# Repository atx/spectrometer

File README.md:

# Alpha Spectrometer

Alpha spectrometer developed during my internship at the [IEAP](http://www.utef.cvut.cz/ieap).

Pu-239 Am-241 Cm-244 spectrum (on bare die BPW34 in vacuum)

## Protocol

### General structure

```
|----------|---------
|   type   | content...
|----------|---------
```

If the device receives a packet with invalid type, it responds with an ERROR
packet with EUNKNOWN error type.

### Host->Device

#### NOP

This does not do anything, it is recommended to send a bunch of NOPs on opening
the serial port to flush any data which might have been left in the device input
buffer.
```
|----------|
|   0x01   |
|----------|
```
#### PING

Used by host to check whether the device is alive. Device should respond with PONG.
```
|----------|
|   0x02   |
|----------|
```
#### GET

Used by host to get basic properties. Device should respond with GETRESP.
```
|----------|---------|
|   0x03   | propid  |
|----------|---------|
```
#### SET

Used by host to set basic properties. Propval length depends on the property being
set. Note that multi byte values should be sent in little endian.
```
|----------|---------|----------
|   0x04   | propid  | propval...
|----------|---------|----------
```
#### START

Start sampling and sending events.
```
|----------|
|   0x05   |
|----------|
```
#### END

End sampling and sending events.
```
|----------|
|   0x06   |
|----------|
```
### Device->Host

The most significant bit of the type field is always set to 1.

#### PONG

Sent as response to host PING.
```
|----------|
|   0x82   |
|----------|
```
#### EVENT

Send event (little endian).
```
|----------|----------|----------|
|   0x87   |   low    |   high   |
|----------|----------|----------|
```
#### GETRESP
```
|----------|----------|----------
|   0x83   |  propid  |  value...
|----------|----------|----------
```
The value length depends on the propid and the byte order is little endian.

#### WAVE

Sends event waveform. This is currently not yet implemented.
```
|----------|----------|----------
|   0x88   |  length  |  <length> samples, 2 bytes each, Big endian
|----------|----------|----------
```
#### ERROR
```
|----------|----------|
|   0xff   |  errno   |
|----------|----------|
```
Sent on errors.
errno:
  =  1  EUNKNOWN
    -- Sent on unknown packet type received
  =  2  EINKEY
    -- Sent on invalid key in GET/SET packet
  =  3  EINOP
    -- Sent on invalid operation on an existing key (unsuported read/write)

### Properties

#### PROP_FW (0x01)
length = 2

Firmware version version.

#### PROP_THRESH (0x02)
length = 2

Event trigger threshold.

#### PROP_BIAS (0x03)
length = 1

Set to 1 if the internal bias generator should be enabled.

#### PROP_AMP (0x04)
length = 1

Set to 1 if the internal x6 amplifier should be enabled.

#### PROP_RTHRESH (0x05)
length = 2

If the value is > 0, the events are further filtered based on whether their falling edge
is at least N samples longer than the rising edge.

#### PROP_SERNO (0x06)
length = 2

Serial number of the device. Set at compile time using `make SERNO=X`

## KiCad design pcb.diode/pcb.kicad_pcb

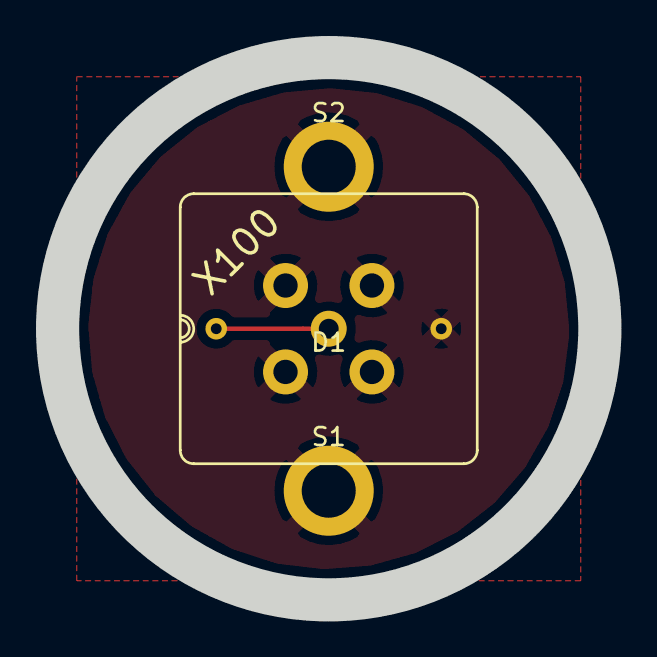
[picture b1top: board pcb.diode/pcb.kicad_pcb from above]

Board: 2 copper layers, 30.1 x 30.1 mm, 4 parts (1 on the bottom side), 2 nets.

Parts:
D1: X100; X100-7-THD
J1: SMA; SMA_STRAIGHT_PCB_LPRS
S1, S2: M2; Measurement_Point_Round-TH_Big

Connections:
unnamed: D1.1, J1.1
unnamed: D1.2, J1.2, J1.3, J1.4, J1.5, S1.1, S2.1

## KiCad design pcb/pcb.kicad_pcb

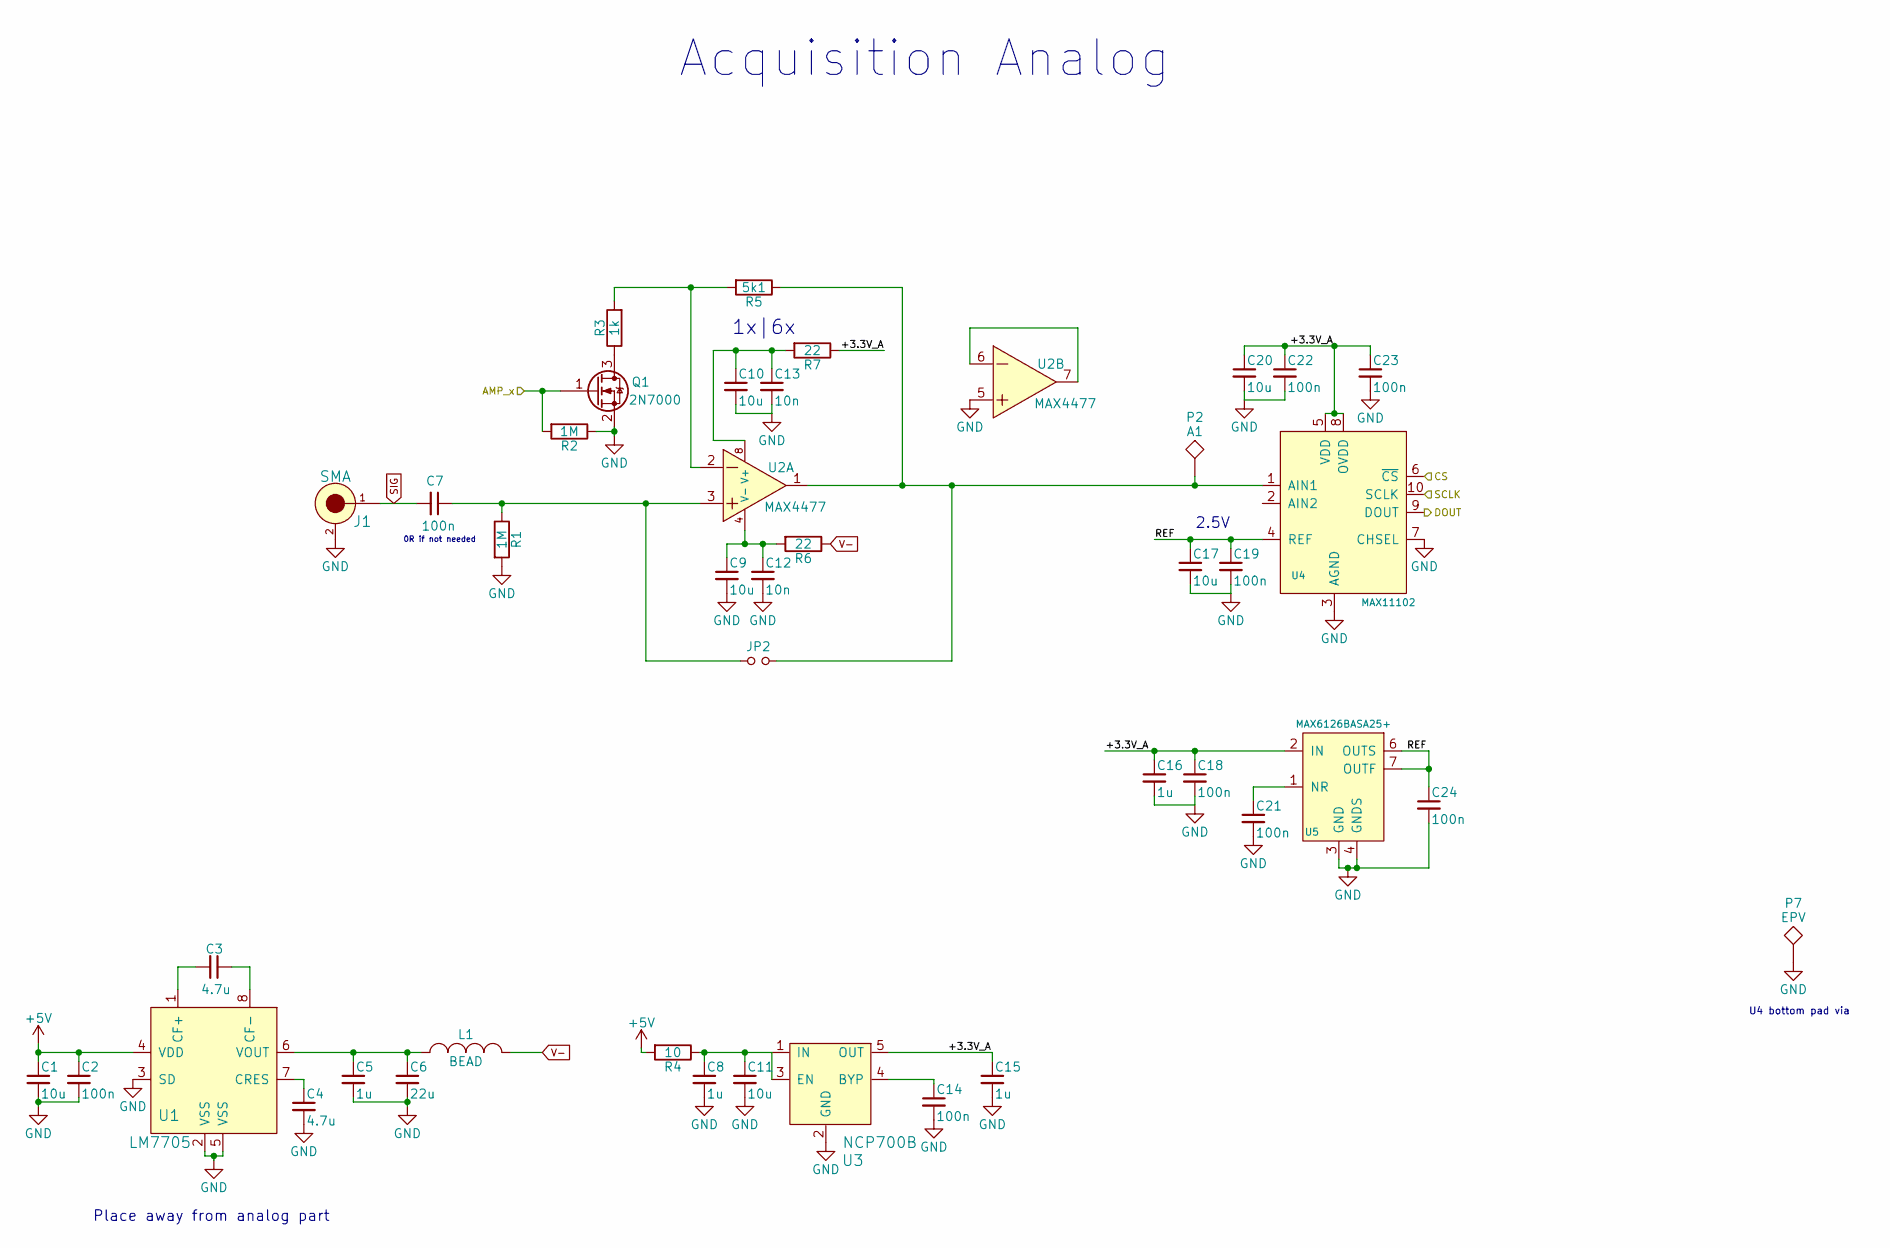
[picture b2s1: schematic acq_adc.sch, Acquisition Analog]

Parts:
C1, C9, C10, C11, C17, C20: 10u; R_0805
C2, C7, C14, C18, C19, C21, C22, C23, C24: 100n; R_0402
C3, C4: 4.7u; R_0603
C5, C8, C15, C16: 1u; R_0402
C6: 22u; R_0805
C12, C13: 10n; R_0402
J1: SMA; CON-SMA-EDGE
JP2: Jumper_NO_Small; R_0402
L1: BEAD; R_0402
P2: A1; Measurement_Point_Round-SMD-Pad_Big
P7: EPV; Measurement_Point_Round-TH_Small
Q1: 2N7000; SOT-23
R1, R2: 1M; R_0402
R3: 1k; R_0402
R4: 10; R_0402
R5: 5k1; R_0402
R6, R7: 22; R_0402
U1: LM7705; MSOP-8_3x3mm_Pitch0.65mm
U2: MAX4477; MSOP-8_3x3mm_Pitch0.65mm
U3: NCP700B; SOT-23-5
U4: MAX11102; uMAX-10-EP
U5: MAX6126BASA25+; SOIC-8_3.9x4.9mm_Pitch1.27mm

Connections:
+5V: C1.1, C2.1, R4.2, U1.4 (VDD); also elsewhere on the board
/acq_adc/+3.3V_A: C15.1, C16.1, C18.1, C20.1, C22.1, C23.1, R7.1, U3.5 (OUT), U4.5 (VDD), U4.8 (OVDD), U5.2 (IN); also elsewhere on the board
/acq_adc/AMP_x: Q1.1 (G), R2.2; also elsewhere on the board
/acq_adc/CS: U4.6 (~CS); also elsewhere on the board
/acq_adc/DOUT: U4.9 (DOUT); also elsewhere on the board
/acq_adc/REF: C17.1, C19.1, C24.1, U4.4 (REF), U5.6 (OUTS), U5.7 (OUTF)
/acq_adc/SCLK: U4.10 (SCLK); also elsewhere on the board
GND: C1.2, C2.2, C4.2, C5.2, C6.2, C8.2, C9.2, C10.2, C11.2, C12.2, C13.2, C14.2, C15.2, C16.2, C17.2, C18.2, C19.2, C20.2, C21.2, C22.2, C23.2, C24.2, J1.2, J1.3, J1.4, J1.5, P7.1, Q1.2 (S), R1.2, R2.1, U1.2 (VSS), U1.3 (SD), U1.5 (VSS), U2.5, U3.2 (GND), U4.3 (AGND), U4.7 (CHSEL), U4.11 (EP), U5.3 (GND), U5.4 (GNDS); also elsewhere on the board
unnamed: C3.1, U1.8 (CF-)
unnamed: C3.2, U1.1 (CF+)
unnamed: C4.1, U1.7 (CRES)
unnamed: C5.1, C6.1, L1.1, U1.6 (VOUT)
unnamed: C10.1, C13.1, R7.2, U2.8 (V+)
unnamed: C8.1, C11.1, R4.1, U3.1 (IN), U3.3 (EN)
unnamed: C9.1, C12.1, R6.2, U2.4 (V-)
unnamed: C14.1, U3.4 (BYP)
unnamed: C21.1, U5.1 (NR)
unnamed: JP2.2, P2.1, R5.1, U2.1, U4.1 (AIN1)
unnamed: Q1.3 (D), R3.1
unnamed 61: R3.2, R5.2, U2.2; also elsewhere on the board
unnamed: U2.6, U2.7
SIG: C7.2, J1.1; also elsewhere on the board
V-: L1.2, R6.1; also elsewhere on the board

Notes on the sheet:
Acquisition Analog
0R if not needed
1x|6x
2.5V
Place away from analog part
U4 bottom pad via

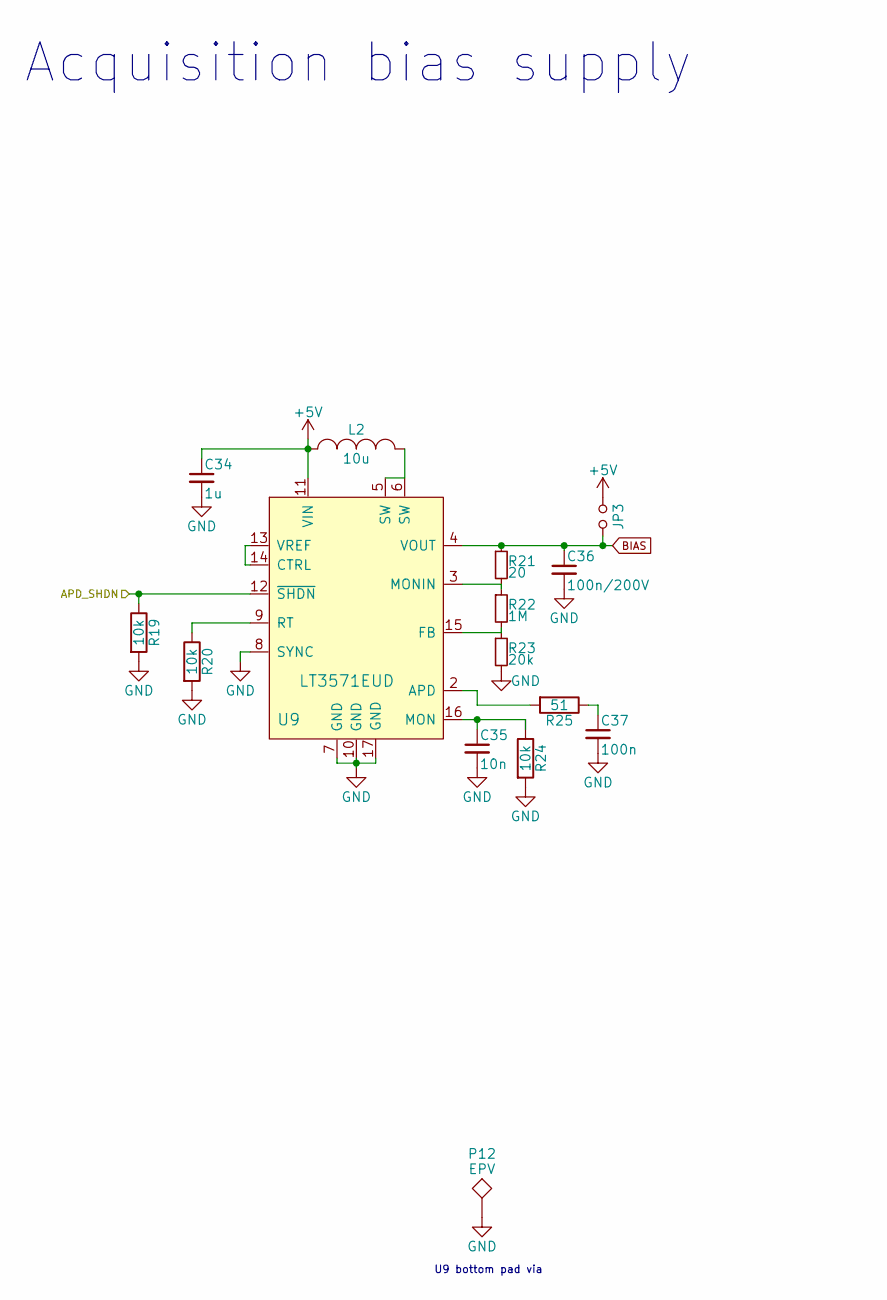
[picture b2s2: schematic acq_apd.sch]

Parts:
C34: 1u; R_0402
C35: 10n; R_0402
C36: 100n/200V; R_0805
C37: 100n; R_0402
JP3: DNP; R_0402
L2: 10u; R_1210
P12: EPV; Measurement_Point_Round-TH_Small
R19, R20, R24: 10k; R_0402
R21: 20; R_0402
R22: 1M; R_0402
R23: 20k; R_0402
R25: 51; R_0402
U9: LT3571EUD; QFN-16-1EP_3x3mm_Pitch0.5mm

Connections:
+5V: C34.1, JP3.1, L2.1, U9.11 (VIN); also elsewhere on the board
/acq_apd/APD_SHDN: R19.1, U9.12 (~SHDN); also elsewhere on the board
BIAS: C36.1, JP3.2, R21.1, U9.4 (VOUT); also elsewhere on the board
GND: C34.2, C35.2, C36.2, C37.2, P12.1, R19.2, R20.2, R23.2, R24.2, U9.7 (GND), U9.8 (SYNC), U9.10 (GND), U9.17 (GND); also elsewhere on the board
unnamed: C35.1, R24.1, U9.16 (MON)
unnamed: C37.1, R25.1
unnamed: L2.2, U9.5 (SW), U9.6 (SW)
unnamed: R20.1, U9.9 (RT)
unnamed: R21.2, R22.1, U9.3 (MONIN)
unnamed: R22.2, R23.1, U9.15 (FB)
unnamed: R25.2, U9.2 (APD)
unnamed: U9.13 (VREF), U9.14 (CTRL)

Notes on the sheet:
Acquisition bias supply
U9 bottom pad via

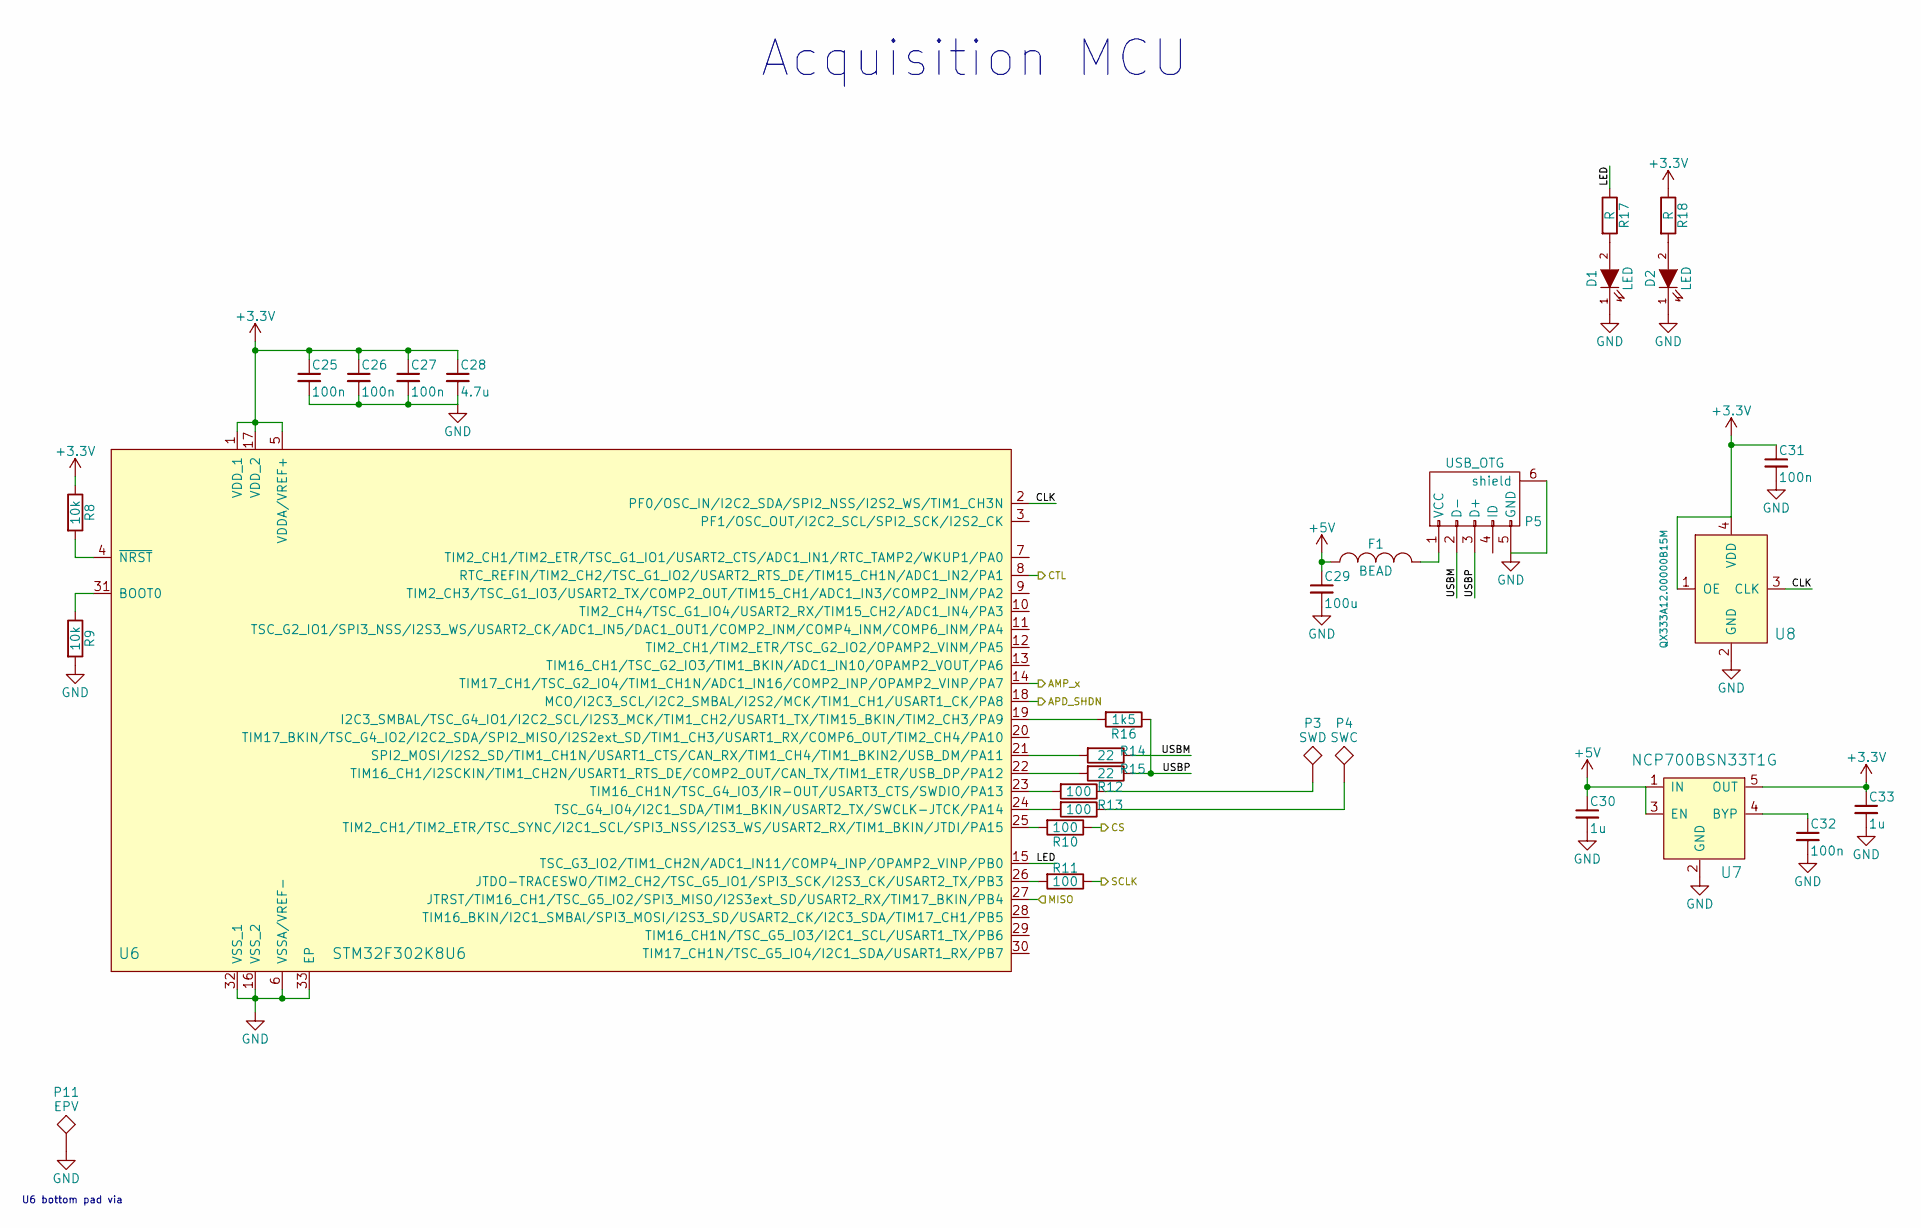
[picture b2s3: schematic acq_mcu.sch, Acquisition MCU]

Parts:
C25, C26, C27, C31, C32: 100n; R_0402
C28: 4.7u; R_0603
C29: 100u; TantalC_SizeB_EIA-3528_Reflow
C30, C33: 1u; R_0402
D1, D2: LED; R_0603
F1: BEAD; R_0402
P3: SWD; Measurement_Point_Round-SMD-Pad_Big
P4: SWC; Measurement_Point_Round-SMD-Pad_Big
P5: USB_OTG; USB_Micro-B
P11: EPV; Measurement_Point_Round-TH_Small
R8, R9: 10k; R_0402
R10, R11, R12, R13: 100; R_0402
R14, R15: 22; R_0402
R16: 1k5; R_0402
R17, R18: R; R_0402
U6: STM32F302K8U6; QFN-32-1EP_5x5mm_Pitch0.5mm
U7: NCP700BSN33T1G; SOT-23-5
U8: QX333A12.00000B15M; QX333A

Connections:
+3V3: C25.1, C26.1, C27.1, C28.1, C31.1, C33.1, R8.1, R18.1, U6.1 (VDD_1), U6.5 (VDDA/VREF+), U6.17 (VDD_2), U7.5 (OUT), U8.1 (OE), U8.4 (VDD)
+5V: C29.1, C30.1, F1.1, U7.1 (IN), U7.3 (EN); also elsewhere on the board
/acq_adc/AMP_x: U6.14 (TIM17_CH1/TSC_G2_IO4/TIM1_CH1N/ADC1_IN1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); also elsewhere on the board
/acq_adc/CS: R10.1; also elsewhere on the board
/acq_adc/DOUT: U6.27 (JTRST/TIM16_CH1/TSC_G5_IO2/SPI3_MISO/I2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); also elsewhere on the board
/acq_adc/SCLK: R11.1; also elsewhere on the board
/acq_apd/APD_SHDN: U6.18 (MCO/I2C3_SCL/I2C2_SMBAL/I2S2/MCK/TIM1_C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); also elsewhere on the board
/acq_mcu/CLK: U6.2 (PF0/OSC_IN/I2C2_SDA/SPI2_NSS/I2S2_WS/TI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), U8.3 (CLK)
/acq_mcu/CTL: U6.8 (RTC_REFIN/TIM2_CH2/TSC_G1_IO2/USART2_RT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); also elsewhere on the board
/acq_mcu/LED: R17.1, U6.15 (TSC_G3_IO2/TIM1_CH2N/ADC1_IN11/COMP4_IN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)
/acq_mcu/USBM: P5.2 (D-), R14.1
/acq_mcu/USBP: P5.3 (D+), R15.1, R16.1
GND: C25.2, C26.2, C27.2, C28.2, C29.2, C30.2, C31.2, C32.2, C33.2, D1.1 (K), D2.1 (K), P5.5 (GND), P5.6 (shield), P11.1, R9.2, U6.6 (VSSA/VREF-), U6.16 (VSS_2), U6.32 (VSS_1), U6.33 (EP), U7.2 (GND), U8.2 (GND); also elsewhere on the board
unnamed: C32.1, U7.4 (BYP)
unnamed: D1.2 (A), R17.2
unnamed: D2.2 (A), R18.2
unnamed: F1.2, P5.1 (VCC)
unnamed: P3.1, R12.1
unnamed: P4.1, R13.1
unnamed: R8.2, U6.4 (~NRST)
unnamed: R9.1, U6.31 (BOOT0)
unnamed: R10.2, U6.25 (TIM2_CH1/TIM2_ETR/TSC_SYNC/I2C1_SCL/SPI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)
unnamed: R11.2, U6.26 (JTDO-TRACESWO/TIM2_CH2/TSC_G5_IO1/SPI3_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)
unnamed: R12.2, U6.23 (TIM16_CH1N/TSC_G4_IO3/IR-OUT/USART3_CTS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)
unnamed: R13.2, U6.24 (TSC_G4_IO4/I2C1_SDA/TIM1_BKIN/USART2_TX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)
unnamed: R14.2, U6.21 (SPI2_MOSI/I2S2_SD/TIM1_CH1N/USART1_CTS/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)
unnamed: R15.2, U6.22 (TIM16_CH1/I2SCKIN/TIM1_CH2N/USART1_RTS_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)
unnamed: R16.2, U6.19 (I2C3_SMBAL/TSC_G4_IO1/I2C2_SCL/I2S3_MCK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)

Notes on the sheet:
Acquisition MCU
U6 bottom pad via

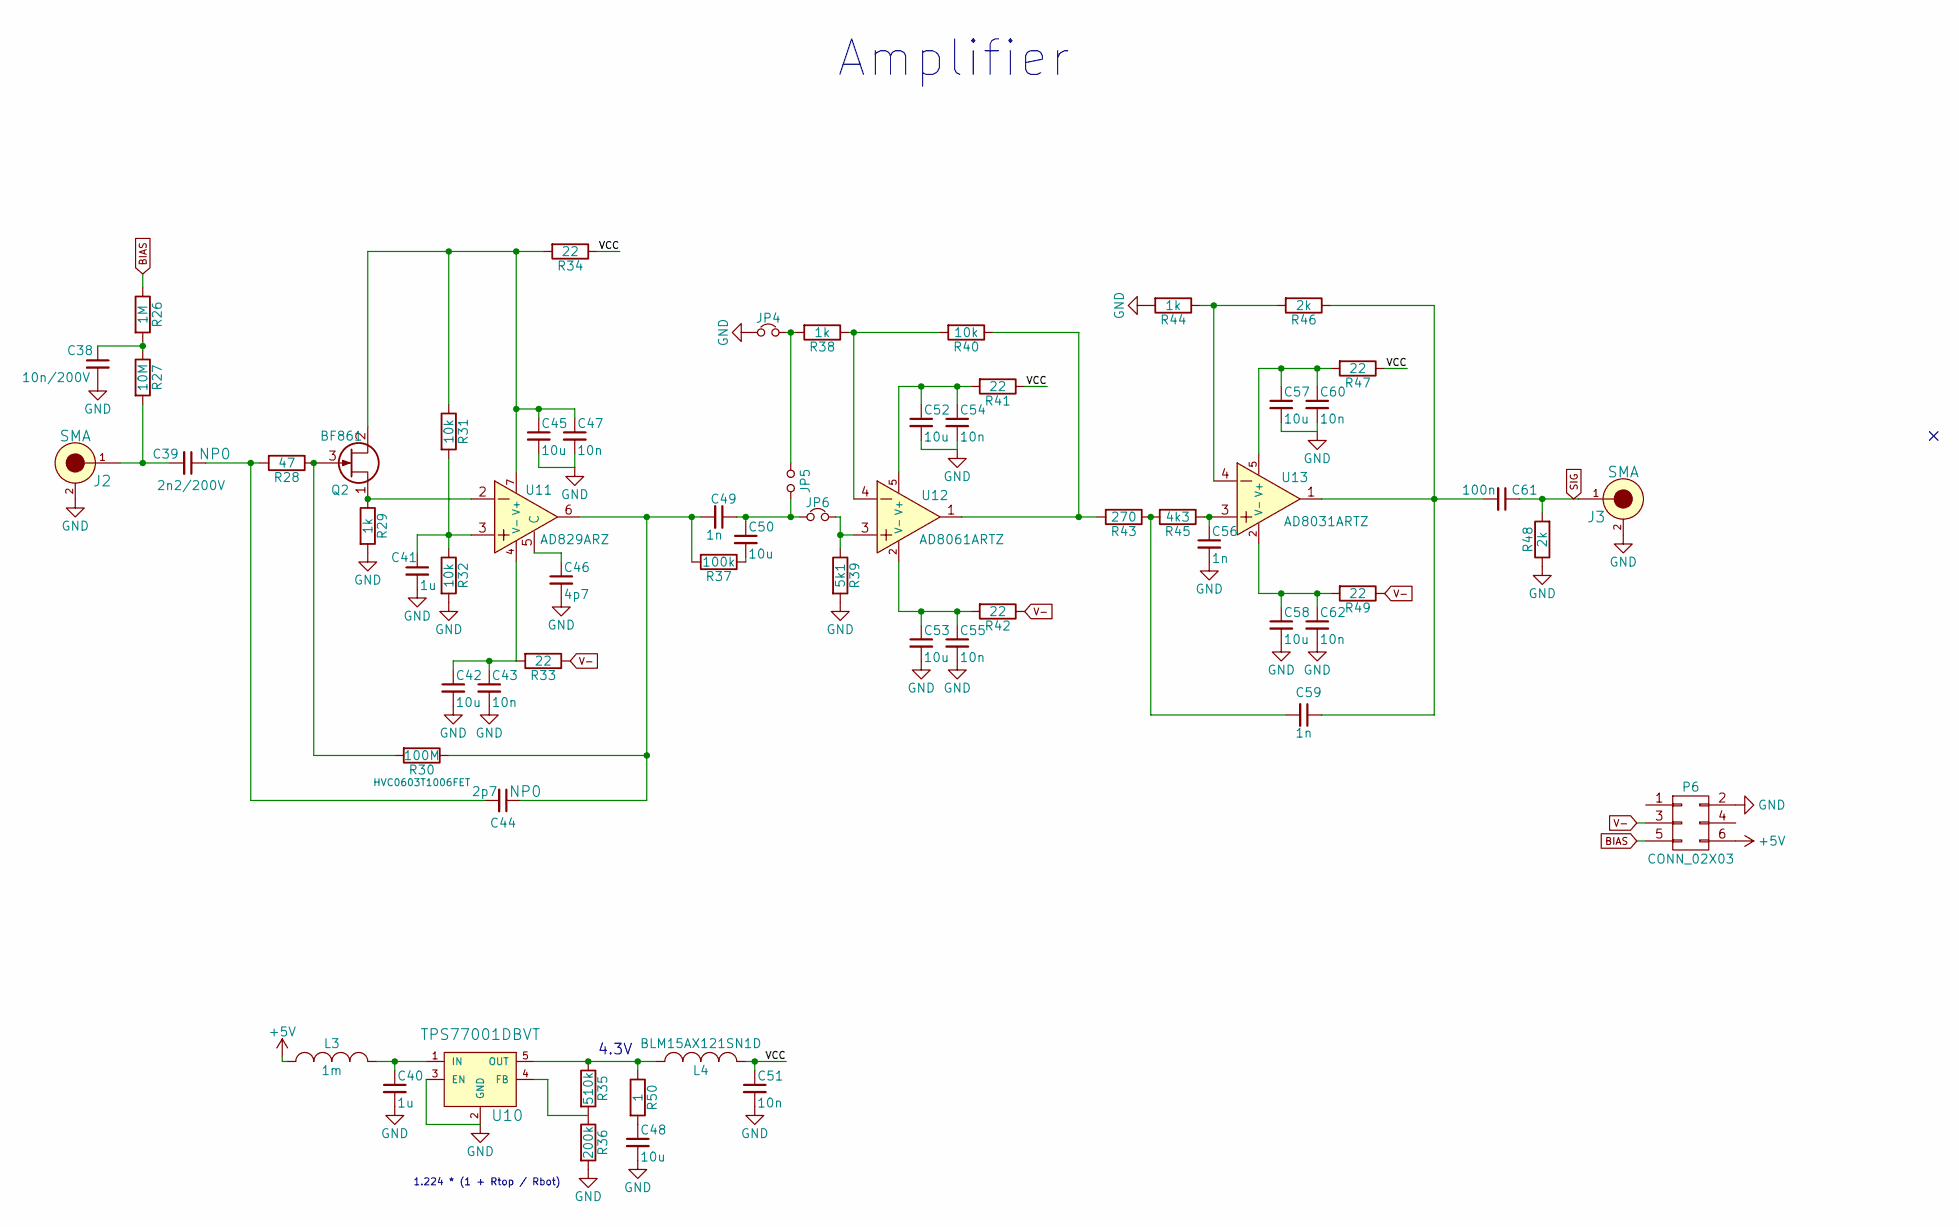
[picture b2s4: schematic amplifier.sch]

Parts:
C38: 10n/200V; R_0805
C39: 2n2/200V; R_0805
C40, C41: 1u; R_0402
C42, C45, C48, C50, C52, C53, C57, C58: 10u; R_0805
C43, C47, C51, C54, C55, C60, C62: 10n; R_0402
C44: 2p7; R_0402
C46: 4p7; R_0402
C49, C56, C59: 1n; R_0402
C61: 100n; R_0402
J2, J3: SMA; CON-SMA-EDGE
JP4, JP6: 0R; R_0402
JP5: DNP; R_0402
L3: 1m; SDR0302
L4: BLM15AX121SN1D; R_0402
P6: CONN_02X03; CONN_02x03_EDGE
Q2: BF861; SOT-23
R26: 1M; R_0402
R27: 10M; R_0402
R28: 47; R_0402
R29, R38, R44: 1k; R_0402
R30: 100M; R_0603
R31, R32, R40: 10k; R_0402
R33, R34, R41, R42, R47, R49: 22; R_0402
R35: 510k; R_0402
R36: 200k; R_0402
R37: 100k; R_0402
R39: 5k1; R_0402
R43: 270; R_0402
R45: 4k3; R_0402
R46, R48: 2k; R_0402
R50: 1; R_0402
U10: TPS77001DBVT; SOT-23-5
U11: AD829ARZ; SOIC-8_3.9x4.9mm_Pitch1.27mm
U12: AD8061ARTZ; SOT-23-5
U13: AD8031ARTZ; SOT-23-5

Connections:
+5V: L3.1, P6.6; also elsewhere on the board
/amplifier/VCC: C51.1, L4.2, R34.1, R41.1, R47.1
BIAS: P6.5, R26.1; also elsewhere on the board
GND: C38.2, C40.2, C41.2, C42.2, C43.2, C45.2, C46.2, C47.2, C48.2, C51.2, C52.2, C53.2, C54.2, C55.2, C56.2, C57.2, C58.2, C60.2, C62.2, J2.2, J2.3, J2.4, J2.5, J3.2, J3.3, J3.4, J3.5, JP4.1, P6.2, R29.2, R32.2, R36.2, R39.2, R44.2, R48.1, U10.2 (GND), U10.3 (EN); also elsewhere on the board
unnamed: C38.1, R26.2, R27.1
unnamed: C39.1, C44.2, R28.2
unnamed: C39.2, J2.1, R27.2
unnamed: C40.1, L3.2, U10.1 (IN)
unnamed: C41.1, R31.2, R32.1, U11.3
unnamed: C42.1, C43.1, R33.2, U11.4 (V-)
unnamed: C44.1, C49.2, R30.1, R37.2, U11.6
unnamed: C45.1, C47.1, Q2.2 (D), R31.1, R34.2, U11.7 (V+)
unnamed: C46.1, U11.5 (C)
unnamed: C48.1, R50.2
unnamed: C49.1, C50.1, JP5.2, JP6.1
unnamed: C50.2, R37.1
unnamed: C52.1, C54.1, R41.2, U12.5 (V+)
unnamed: C53.1, C55.1, R42.2, U12.2 (V-)
unnamed: C56.1, R45.1, U13.3
unnamed: C57.1, C60.1, R47.2, U13.5 (V+)
unnamed: C58.1, C62.1, R49.2, U13.2 (V-)
unnamed: C59.1, C61.2, R46.1, U13.1
unnamed: C59.2, R43.1, R45.2
unnamed: JP4.2, JP5.1, R38.2
unnamed: JP6.2, R39.1, U12.3
unnamed: L4.1, R35.1, R50.1, U10.5 (OUT)
unnamed: Q2.1 (S), R29.1, U11.2
unnamed: Q2.3 (G), R28.1, R30.2
unnamed: R35.2, R36.1, U10.4 (FB)
unnamed: R38.1, R40.2, U12.4
unnamed: R40.1, R43.2, U12.1
unnamed: R44.1, R46.2, U13.4
SIG: C61.1, J3.1, R48.2; also elsewhere on the board
V-: P6.3, R33.1, R42.1, R49.1; also elsewhere on the board

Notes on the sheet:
Amplifier
4.3V
1.224 * (1 + Rtop / Rbot)

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
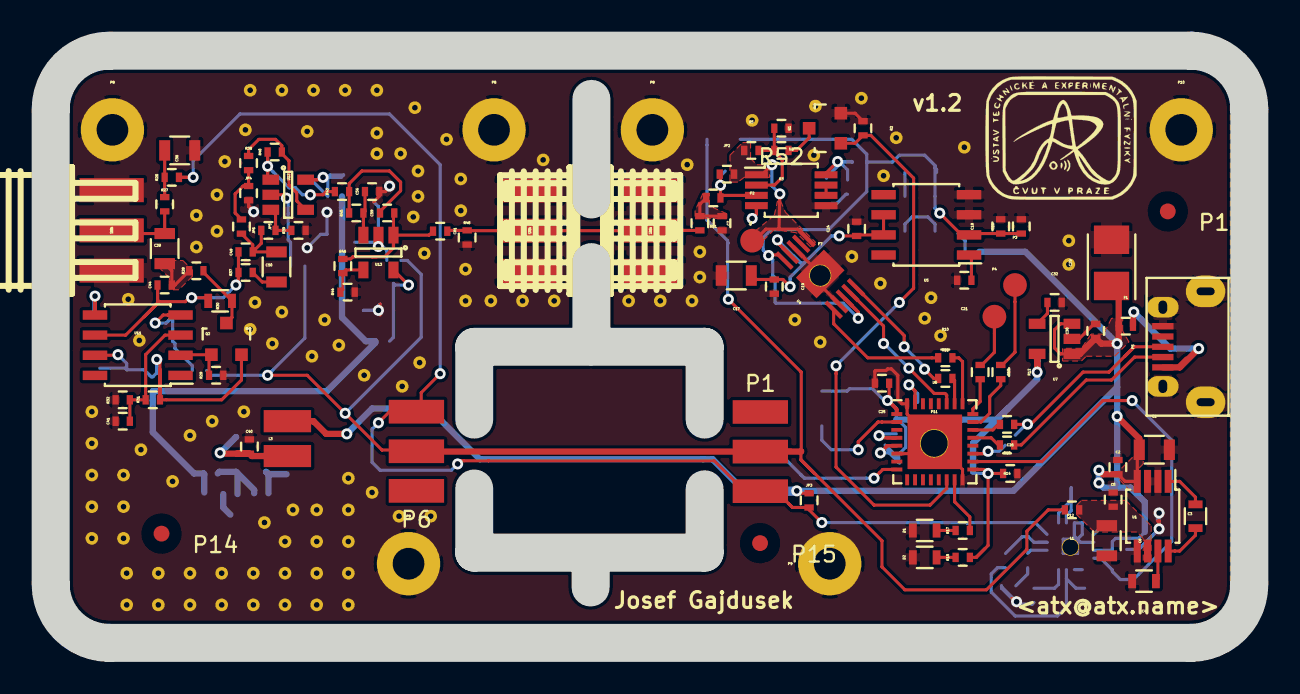
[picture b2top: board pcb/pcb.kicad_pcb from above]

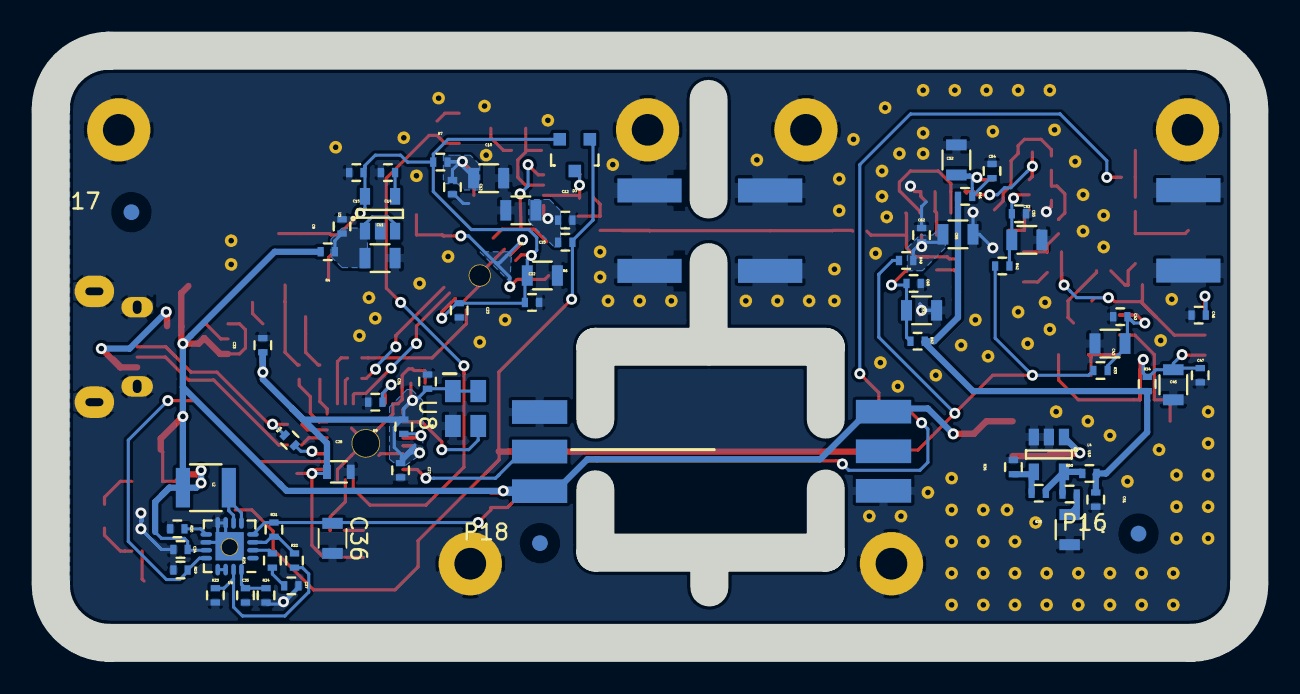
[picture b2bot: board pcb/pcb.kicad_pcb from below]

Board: 2 copper layers, 75.7 x 37.4 mm, 166 parts (66 on the bottom side), 85 nets.

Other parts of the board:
D3: BAT54S-7-F; SOT-23
P1: CONN_02X03; CONN_02x03_EDGE
P8, P8#2, P8#3, P8#4, P9, P10: TST; Measurement_Point_Round-TH_Big
P13, P14, P15, P16, P17, P18: FID; Fiducial_1mm_Dia_2.54mm_Outer_CopperTop
R51: 10k; R_0402
R52: 5k1; R_0402

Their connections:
+5V: P1.6; also elsewhere on the board
/acq_adc/+3.3V_A: D3.2; also elsewhere on the board
/acq_mcu/CTL: P1.4; also elsewhere on the board
BIAS: P1.5; also elsewhere on the board
GND: P1.2, P8.1, P8#2.1, P8#3.1, P8#4.1, P9.1, P10.1, R52.1; also elsewhere on the board
unnamed 61: R52.2; also elsewhere on the board
V-: D3.1, P1.3; also elsewhere on the board

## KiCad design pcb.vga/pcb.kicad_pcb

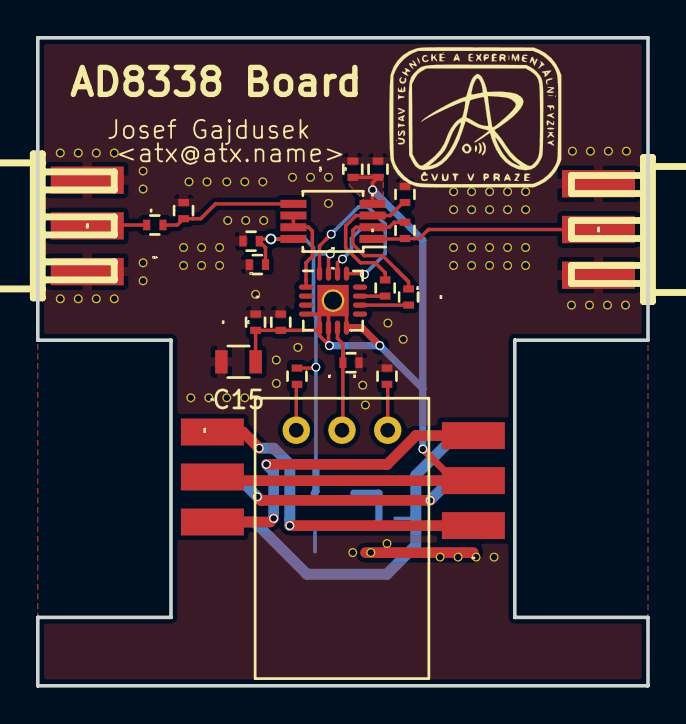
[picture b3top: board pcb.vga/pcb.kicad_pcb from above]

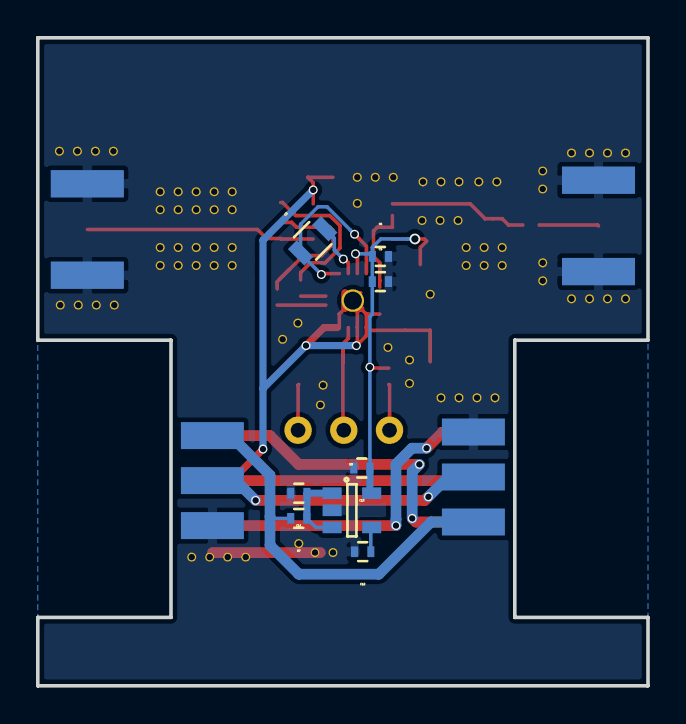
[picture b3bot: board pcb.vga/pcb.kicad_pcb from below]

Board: 2 copper layers, 33.9 x 36.0 mm, 31 parts (8 on the bottom side), 22 nets.

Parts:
C1, C3, C4, C7, C8: 10n; R_0402
C2, C15: 10u; R_0805
C5, C6, C9, C10, C12: 100n; R_0402
C11, C13: 1u; R_0402
C14: DNP; R_0402
J1, J2: SMA; CON-SMA-EDGE
P1: CONN_IN; CONN_02x03_EDGE
P2: CONN_OUT; CONN_02x03_EDGE
R1: 43k; R_0402
R2: 18k; R_0402
R3, R4, R5, R6: 10k; R_0402
R7: 22; R_0402
R8: 1M; R_0402
RV1: 20k; Potentiometer_Bourns_3296W_3-8Zoll_Inline_ScrewUp_Side
U1: MAX4477; MSOP-8_3x3mm_Pitch0.65mm
U2: AD8338; UQFN-16-1EP_3x3mm_Pitch0.5mm
U3: NCP700B; SOT-23-5

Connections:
+3V3: C3.1, C5.1, C7.1, C9.1, C13.1, R1.1, U1.8, U2.15, U3.5
+5V: P1.6, P2.6, R7.2
GND: C1.2, C3.2, C4.2, C5.2, C6.2, C7.2, C8.2, C9.2, C10.2, C11.2, C12.2, C13.2, C15.2, J1.2, J1.3, J1.4, J1.5, J2.2, J2.3, J2.4, J2.5, P1.2, P2.2, R2.2, R5.2, R8.2, U3.2
unnamed: C1.1, RV1.2, U2.7
unnamed: C2.1, U2.13, U2.16
unnamed: C2.2, U2.14
unnamed: C11.1, R7.1, U3.1, U3.3
unnamed: C12.1, U3.4
unnamed: C14.1, R8.1, U1.5
unnamed: C14.2, J1.1
unnamed: J2.1, R6.1, U1.1
unnamed: P1.1, P2.1
unnamed: P1.4, P2.4
unnamed: P1.5, P2.5
unnamed: R1.2, RV1.3
unnamed: R2.1, RV1.1
unnamed: R3.1, R6.2, U1.2
unnamed: R3.2, U2.10
unnamed: R4.1, R5.1, U1.3
unnamed: R4.2, U2.11
unnamed: U1.6, U1.7, U2.1
V-: C4.1, C6.1, C8.1, C10.1, C15.1, P1.3, P2.3, U1.4, U2.4, U2.5, U2.6, U2.8, U2.17

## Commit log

2016-05-31 Initial commit #2
2016-05-31 .gitignore update
2016-06-12 interface: Switch spectrometer drivers to asyncio
2016-06-12 pcb: Update to v1.1
    Changes:
    Add input protection diodes to acquisition board
    Add second screw hole to the preamplifier
    Add PCB revision number to the board
    LPF->HPF at the output of the preamplifier board
    Fix connector orientation on the preamplifier board
2016-06-12 pcb.vga: Add the AD8338 board
    Also accidentaly added some changes which belonged to 2e3d88cac247fd0d2ffe4990b1f29d498317d67b
    but too lazy to fix
2016-06-13 interface: spectrometer.SerSpect: Behave correctly if some packet-receiving method gets called from multiple coroutines
2016-06-14 interface: Add favicon.ico
2016-06-14 src: Remove .o .elf .map... files
2016-06-14 src: Add ratio threshold support
2016-06-14 interface: Add support for setting configuration values from the web interface
2016-06-23 pcb: Add .pdf and remove plot files
2016-06-23 src: Add proper serial number support
2016-06-23 src: Add periodic packet flushing
2016-07-20 py: Move to an installable library
2016-07-20 web: "Threshold: " -> "Discrimination: " label
2016-07-20 py: DummySpectrometer: Fix channel range
2016-07-21 src: Use half transfer interrupt instead of two separate buffers
2016-07-21 src: Actually properly stop acquisition in acq_pause
2016-07-21 src: Do send zero length packets
2016-07-21 src: Blink when acquiring.
2016-07-25 ieapspect-filedump: Update so that it actually works with the current library
2016-08-01 src: Disable RTHRESH by default as it seems to produce artifacts
2016-08-01 src: Do not send events if the event rate is too high
2016-08-02 py: Make the web files part of the package
    Now ieapspect-web works when installed as a part of the package.
2016-08-02 ieapspect-filedump: Add timestamp option
2016-08-03 src: Rewrite the TX buffer as a proper FIFO, preventing partial packet sends
2016-08-15 Add LICENSE file
2016-08-17 py: Add Spectrig and Fitpix support
2016-08-17 py: Select by USB product description in AsyncSerialSpectrometers
2016-08-17 py: .gitignore update
2016-08-18 py: Fixup the object interface
2017-03-22 py: ieapspect-web: Add autosave
2017-03-23 py: Fix missing time import
2017-05-25 Set default threshold to 50
2017-08-14 py: ieapspect-web: Don't cover the axis with bars while zooming
2017-08-14 py: ieapspect-web: Use solid line for the axis
2017-08-14 src: Remove extraneous empty file
2017-08-15 Add rudimentary DFU bootloader
    Still leaves ton to be desired at the moment.
2017-08-15 pcb: Update to the current iteration
    Looks like I forgot to commit the changes made for manufacturing...
2017-08-15 bootloader: Add LGPL headers
2017-08-15 bootloader: React properly to USB reset request.
    This allows using dfu-util -R
2017-08-16 src/bootloader: Link shared symbols in a slightly less hacky way
2017-08-21 bootloader: Check CRC of the main application
2017-08-21 src|bootloader: Uncomment info printfs in Makefiles
2017-08-21 src|bootloader: Mark the stack section with NOLOAD
    It's not really necessary to initialize the stack when flashing through gdb.
2017-08-21 bootloader: crc.c: Remove debug function
2017-08-21 src|bootloader: Move shared stuff to a dedicated directory
2017-08-21 .gitignore: Add *.bin files
2017-08-21 bootloader: crc: Disable the CRC peripheral after calculating the checksum
2017-08-22 py: ieapspect-web: Fix bottom-of-histogram bar flicker
2017-08-22 py: ieapspect-web: Use window.requestAnimationFrame
    Does not seem to help all that much, but it is hopefully a step in the right
    direction.
2017-11-24 py: ieapspect-web: Actually make the --bind parameter do something
2017-11-24 py: Stylistic patches
2017-11-24 py: Move to a better directory
    ./interface/py was historical baggage anyway
2017-12-15 pcb.diode: Add
2018-01-12 acq: Don't drop all events when overflow occurs
2018-02-05 py: Use serial_asyncio instead of serial.aio
2018-03-16 py: web: Fix dummy spectrometer
2018-03-16 py: web: Fix for aiohttp 3.0
    Meeeh, API changes...
2018-03-19 setup: Don't build/install the ftdi wrappers
    Not really complete anyway...
2018-03-19 py: web: Improve protection against CSRF/DNS Rebinding
    The CSRF-token way was vulnerable against DNS rebinding, this way is somewhat
    better
2018-04-20 python: debian: Add packaging metadata
2018-05-18 mechanical: diode: Add
2018-10-10 src: Bypass the output FIFO when sending command responses
    Still not ideal but now we can do 10k/s events no problem
